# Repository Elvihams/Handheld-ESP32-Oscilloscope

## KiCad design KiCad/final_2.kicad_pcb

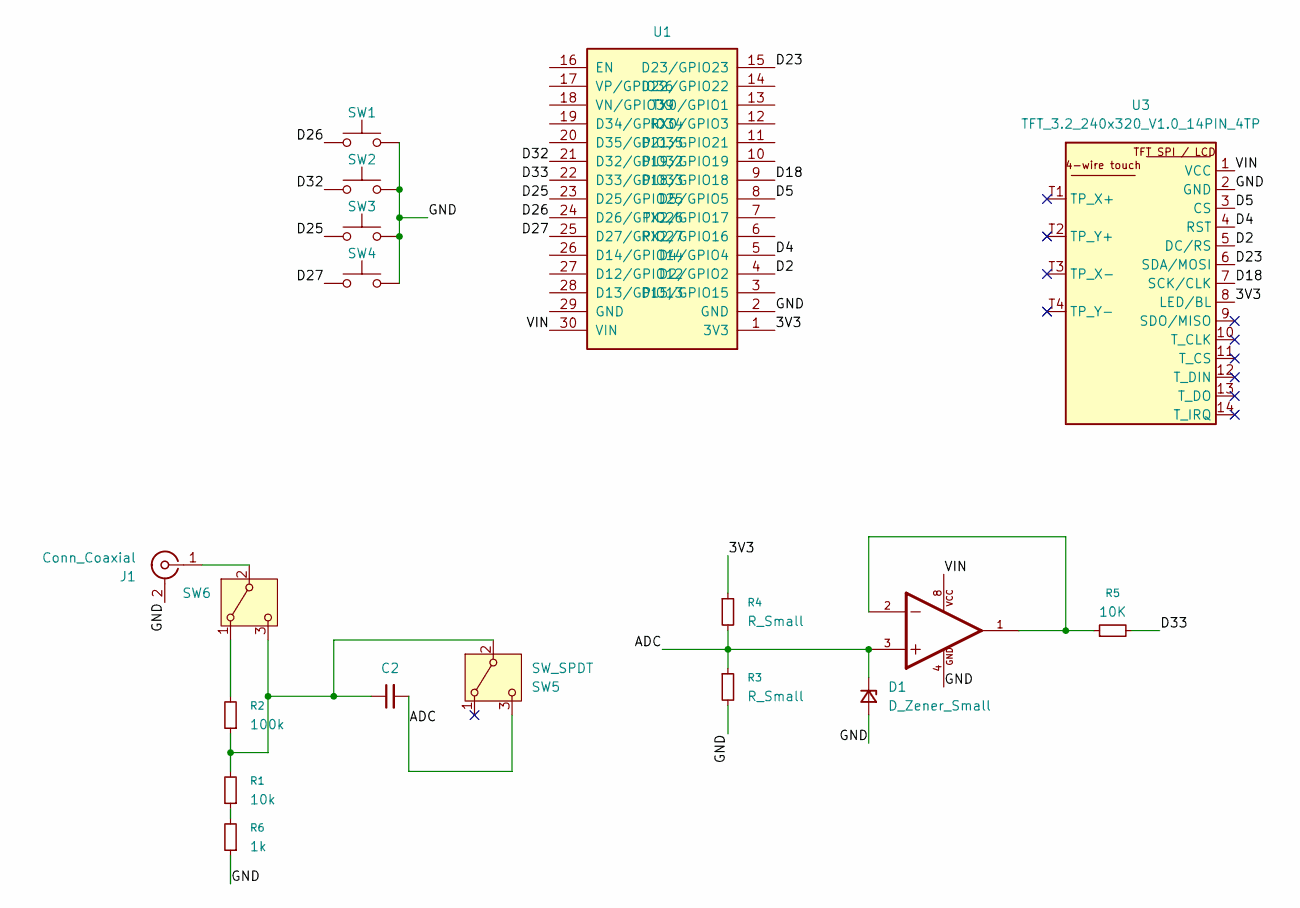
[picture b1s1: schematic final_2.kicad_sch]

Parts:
C2: C_Small; C_Disc_D5.0mm_W2.5mm_P2.50mm
D1: D_Zener_Small; D_DO-201_P12.70mm_Horizontal
J1: Conn_Coaxial; BNC_Amphenol_B6252HB-NPP3G-50_Horizontal
R1: 10k; R_Axial_DIN0204_L3.6mm_D1.6mm_P5.08mm_Horizontal
R2: 100k; R_Axial_DIN0204_L3.6mm_D1.6mm_P5.08mm_Horizontal
R3, R4: R_Small; R_Axial_DIN0204_L3.6mm_D1.6mm_P5.08mm_Horizontal
R5: 10K; R_Axial_DIN0204_L3.6mm_D1.6mm_P5.08mm_Horizontal
R6: 1k; R_Axial_DIN0204_L3.6mm_D1.6mm_P5.08mm_Horizontal
SW1, SW2, SW3, SW4: SW_Push; SW_PUSH-12mm_Wuerth-430476085716
SW5, SW6: SW_SPDT; PinSocket_1x05_P2.54mm_Vertical
U1: ESP32_DevKitV1_30pin
U2: LM358N; DIP8_300; PARTREV 1.0.3
U3: TFT_3.2_240x320_V1.0_14PIN_4TP; PinSocket_1x08_P2.54mm_Vertical

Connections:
/3V3: R4.1, U1.1 (3V3), U3.8 (LED/BL)
/ADC: C2.2, D1.1 (K), R3.1, R4.2, SW5.3 (C), U2.3
/D2: U1.4 (D2/GPIO2), U3.5 (DC/RS)
/D4: U1.5 (D4/GPIO4), U3.4 (RST)
/D5: U1.8 (D5/GPIO5), U3.3 (CS)
/D18: U1.9 (D18/GPIO18), U3.7 (SCK/CLK)
/D23: U1.15 (D23/GPIO23), U3.6 (SDA/MOSI)
/D25: SW3.1, U1.23 (D25/GPIO25)
/D26: SW1.1, U1.24 (D26/GPIO26)
/D27: SW4.1, U1.25 (D27/GPIO27)
/D32: SW2.1, U1.21 (D32/GPIO32)
/D33: R5.2, U1.22 (D33/GPIO33)
/GND: D1.2 (A), J1.2 (Ext), R3.2, R6.1, SW1.2, SW2.2, SW3.2, SW4.2, U1.2 (GND), U2.4, U3.2 (GND)
/VIN: U1.30 (VIN), U2.8, U3.1 (VCC)
unnamed: J1.1 (In), SW6.2 (B)
unnamed: R1.1, R6.2
unnamed: R5.1, U2.1, U2.2
unnamed: C2.1, R1.2, R2.1, SW5.2 (B), SW6.3 (C)
unnamed: R2.2, SW6.1 (A)

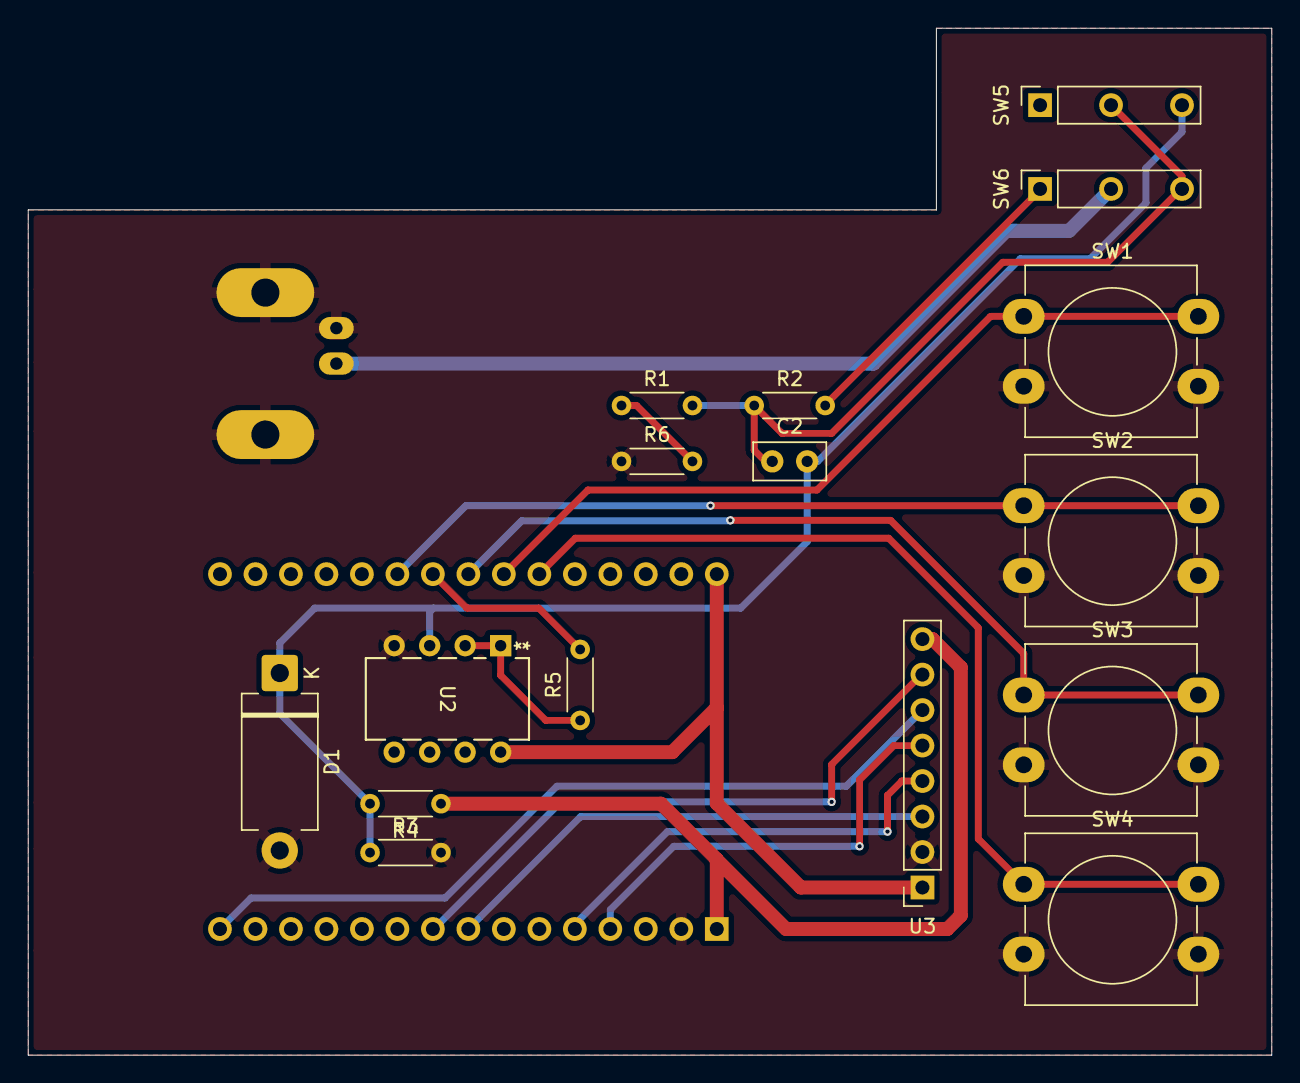
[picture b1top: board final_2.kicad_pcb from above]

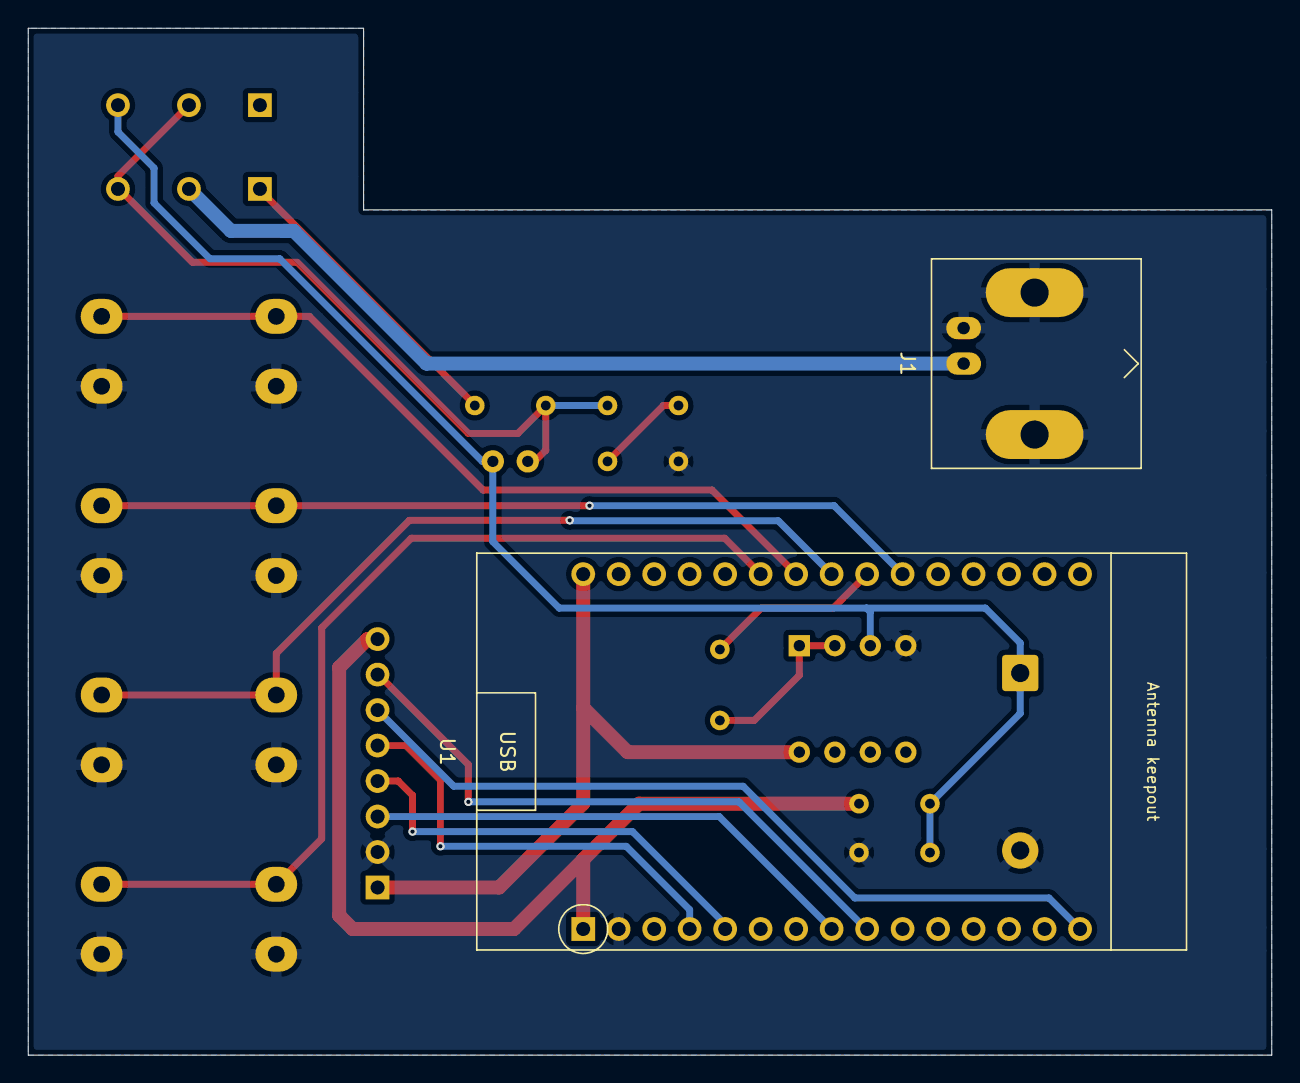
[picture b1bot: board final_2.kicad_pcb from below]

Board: 2 copper layers, 89.0 x 73.5 mm, 18 parts (2 on the bottom side), 19 nets.
